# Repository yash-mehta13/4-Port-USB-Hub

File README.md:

# 4-Port USB Hub (USB Hub Port Extender)

A KiCad 8 design for a self-powered 4-port USB hub board. The schematic names a Genesys Logic **GL850G** hub controller (`IC1`, value `GL850G-HH`), one upstream USB-A connector (`J5`), four downstream USB-A connectors (`J1`–`J4`), a DC barrel-jack power input (`CN1`), per-port polyfuses, ferrite beads and bulk capacitors, SRV05-4 ESD arrays, a 12 MHz crystal, and a gang-mode LED.

> **Status: design in progress — not ready for fabrication.**
> A source-level audit (see [docs/validation-report.md](docs/validation-report.md)) found several connectivity defects in the schematic and PCB, including a **net that ties USB port 2's D− line to the 5 V rail**, **swapped D+/D− on port 1**, an **unconnected reset input**, and a **hub-controller symbol that is actually a Microchip MCP23017 I/O-expander symbol**. No board has been fabricated or tested, no KiCad ERC/DRC has been run (KiCad was not available in the audit environment), and no USB compliance claim is made. Details in [Known issues](#known-issues).

## Contents
[Purpose](#purpose) · [Images](#project-images) · [Design summary](#design-summary) · [Specifications](#specifications) · [Opening the project](#opening-the-project) · [Libraries and models](#custom-libraries-and-3d-models) · [Validation status](#validation-status) · [Known issues](#known-issues) · [BOM](#bill-of-materials) · [Fabrication](#fabrication-workflow) · [Safety](#safety-and-limitations) · [Docs](#documentation) · [License](#license-and-attribution) · [Roadmap](#future-improvements) · [Contributing](#contributing)

## Purpose
A USB hub turns one host USB port into several. This project is a learning/portfolio hardware design that implements a hub on a custom 4-layer board using a single-chip hub controller, with an external 5 V barrel-jack supply so downstream ports are not powered solely from the host. See [docs/project-overview.md](docs/project-overview.md).

## Project images
All images are real KiCad screenshots of this design (taken 2026-01-22/23, i.e. intermediate states of the design, not a verified final revision). **There is no photograph of a fabricated or assembled board in this repository.**

| | |
|---|---|
|  |  |
| 3D viewer, top view: five USB-A connectors, DC jack, HC-49 crystal, SSOP-28 hub IC. | 3D viewer, perspective: through-hole radial bulk capacitors, mixed horizontal connector styles. |

*Single-sheet schematic (A4, dated 2026-01-12): downstream ports, hub controller, reset, gang indicator, crystal, upstream, overcurrent network and external power.*

### Gallery
| Image | Content |
|---|---|
| [pcb-layout-all-layers.png](docs/images/pcb-layout-all-layers.png) | PCB editor, all layers visible, board with zone fills |
| [pcb-layout-bottom-active.png](docs/images/pcb-layout-bottom-active.png) | PCB editor, back copper highlighted (large "KiCad" logo text is on `B.Cu`) |
| [schematic-downstream-and-controller.png](docs/images/schematic-downstream-and-controller.png) | Downstream ports J1–J4 with IC2/IC3 and hub controller IC1 |
| [schematic-upstream-and-overcurrent.png](docs/images/schematic-upstream-and-overcurrent.png) | Upstream J5/IC4 and the overcurrent divider (R6/R7) |
| [schematic-reset-gang-crystal-power.png](docs/images/schematic-reset-gang-crystal-power.png) | Reset network, gang LED, crystal, external power and Q1 |

## Design summary
* **Controller:** `IC1`, value `GL850G-HH`, 28-pin SSOP footprint. Genesys Logic is the manufacturer *implied by the value*; the official datasheet could not be retrieved during the audit, so the pin map is **not verified** (see D1 in [circuit-design](docs/circuit-design.md)).
* **Upstream:** `J5` (Type-A) → `IC4` SRV05-4 → hub pins 25/26 (`USB0_N`/`USB0_P`). Upstream VBUS passes through ferrite `L1` to net `+5V`.
* **Downstream:** `J1`–`J4` ↔ `USB1`–`USB4` pairs on hub pins 27/28, 2/3, 8/9, 11/12; ESD arrays `IC2` (ports 1–2) and `IC3` (ports 3–4). Each port has a 500 mA-labelled polyfuse (`R1`–`R4`), ferrite bead (`L2`–`L5`), 100 µF + 0.1 µF.
* **Power:** barrel jack `CN1` → rail `VCC`; `Q1` (P-MOSFET) links `+5V` (host VBUS) and `VCC`. Hub analog rail `AVDD` is `DVDD` through ferrite `L6`.
* **Clock:** `Y1` 12 MHz, 2×33 pF.
* **Board:** 55 mm × 65 mm, 4 copper layers (`F.Cu`, `In1.Cu`=GND zone, `In2.Cu`=`+5V` zone, `B.Cu`), 1.6 mm. 45 vias (0.6/0.3 mm), all tracks 0.2 mm.

## Specifications
Only values read from the design files are listed.

| Item | Value | Source |
|---|---|---|
| Hub controller (per value field) | GL850G-HH, SSOP-28 footprint | schematic/PCB |
| Downstream / upstream connectors | 4 / 1 USB Type-A | schematic |
| Crystal | 12 MHz, 18 pF load (library description), 2×33 pF | schematic + library |
| Port polyfuses | value labelled 500 mA (part unspecified) | schematic |
| ESD arrays | 3× SRV05-4 | schematic |
| Board size | 55 × 65 mm | PCB Edge.Cuts |
| Layers / thickness | 4 / 1.6 mm (stackup in file; see caveats) | PCB |
| Net class | `USD_diff`: 0.2 mm width, 0.15 mm gap (applies to `USB*`) | project settings |
| Supply voltage, current budget, USB speed | **not specified in the design** | — |

USB speed is not asserted here: the supported speeds must be taken from the controller datasheet once the part is confirmed, and compliance has not been tested.

## Opening the project
1. Install KiCad 8.x (project files were saved by KiCad 8.0: schematic format `20231120`, PCB format `20240108`). KiCad 7 cannot open them.
2. Open `USB Hub Port Extender.kicad_pro`.
3. Standard KiCad libraries (symbols, footprints, `${KICAD8_3DMODEL_DIR}` 3D models) must be installed. The schematic embeds its symbols; footprints are resolved from KiCad's stock libraries.
4. Full steps: [docs/fabrication-guide.md](docs/fabrication-guide.md#reproducing-the-review).

## Custom libraries and 3D models
The root holds SnapEDA-style library downloads: `ECS-120-18-4X-CKM`, `MCP23017-E_SS`, `PMV20EN` (`.kicad_sym`, footprints, `.step`, `.zip`). **The current design instantiates none of their footprints**, and the repo has no `sym-lib-table`/`fp-lib-table`. Only the `ECS-120-18-4X-CKM` and `MCP23017-E_SS` *symbols* are embedded in the schematic (the latter wrongly, as `IC1`). See [docs/licensing-and-attribution.md](docs/licensing-and-attribution.md) and [circuit-design](docs/circuit-design.md#library-usage).

## Validation status
| Check | Status |
|---|---|
| KiCad ERC | **Not run** (KiCad 8 / `kicad-cli` unavailable) |
| KiCad DRC | **Not run** |
| Schematic ↔ PCB net comparison | Run with `tools/audit_netlist.py` (independent script): one difference (`J1` pin 5) |
| Gerber / drill / BOM / STEP export | **Not run** |
| Physical build, enumeration, USB compliance, ESD, thermal | **Not done** |

## Known issues
Full list with evidence: [docs/validation-report.md](docs/validation-report.md) and [docs/circuit-design.md](docs/circuit-design.md).

1. **D2 – VCC rail merged with `USB2_N`:** global label `USB2_N` sits on the VCC distribution wire; the PCB carries the same merged net. `J2` pin 2 (D−), `IC1` pins 2 and 23, SRV05-4 pins, `Q1`, `CN1` pin 1 and all four polyfuse inputs share one net.
2. **D3 – port 1 D+/D− swapped:** `J1` pin 2 (D−) is on `USB1_P`, pin 3 (D+) on `USB1_N`; `J2`–`J5` are wired D−→`_N`.
3. **D1 – `IC1` symbol is an MCP23017:** pin names (`GPA*`, `SCL`, `SDA`…) and SnapEDA properties belong to an I²C I/O expander.
4. **D4 – `RESET#` not connected to the reset RC network** (`R8`/`R9`/`C15`).
5. **D5 – overcurrent label typo:** `OVCURR1#` (R6/R7) vs `OVCURR#1` (IC1 pin 21).
6. **D6 – `J1` pin 5:** unconnected in schematic, `GND` in PCB.
7. Layout risks: 0.2 mm tracks carry VBUS/VCC; USB pair length mismatch (e.g. `USB4`); impedance unverified.

## Bill of materials
[docs/bill-of-materials.csv](docs/bill-of-materials.csv) – 54 parts grouped by value, matching all 54 PCB footprints. Most manufacturer part numbers are **unresolved** (the design stores generic values only); no sourcing links or prices are invented.

## Fabrication workflow
Summarised in [docs/fabrication-guide.md](docs/fabrication-guide.md). Do not order boards until the defects above are fixed, ERC/DRC are clean or justified, the fabricator's capabilities and stackup are agreed, and the impedance question is resolved.

## Safety and limitations
Unprotected tests of an unvalidated design can short VBUS to data lines or back-feed a host. Read [docs/safety-and-limitations.md](docs/safety-and-limitations.md) and [docs/hardware-validation.md](docs/hardware-validation.md) before powering any assembled board.

## Documentation
| Document | Purpose |
|---|---|
| [project-overview](docs/project-overview.md) | scope, artifacts, status |
| [circuit-design](docs/circuit-design.md) | schematic walkthrough and defects |
| [pcb-layout-review](docs/pcb-layout-review.md) | layers, routing, USB/power concerns |
| [bill-of-materials.csv](docs/bill-of-materials.csv) | components |
| [fabrication-guide](docs/fabrication-guide.md) | outputs and reproduction steps |
| [validation-report](docs/validation-report.md) | what was and wasn't run |
| [hardware-validation](docs/hardware-validation.md) | bench checklist (all unchecked) |
| [safety-and-limitations](docs/safety-and-limitations.md) | risks |
| [troubleshooting](docs/troubleshooting.md) | symptoms → causes |
| [decisions-and-roadmap](docs/decisions-and-roadmap.md) | design decisions and ideas |
| [licensing-and-attribution](docs/licensing-and-attribution.md) | license state |
| [docs/reports/](docs/reports/) | script-generated netlists/statistics |

## License and attribution
**No LICENSE file exists**, so no open-source permissions are granted by default; the owner must choose a license. Third-party library content (SnapEDA downloads, KiCad stock libraries) is covered in [docs/licensing-and-attribution.md](docs/licensing-and-attribution.md). Author: [yash-mehta13](https://github.com/yash-mehta13).

## Future improvements
See [docs/decisions-and-roadmap.md](docs/decisions-and-roadmap.md). Add a real board photograph and bench-test report once hardware exists.

## Contributing
See [CONTRIBUTING.md](CONTRIBUTING.md).

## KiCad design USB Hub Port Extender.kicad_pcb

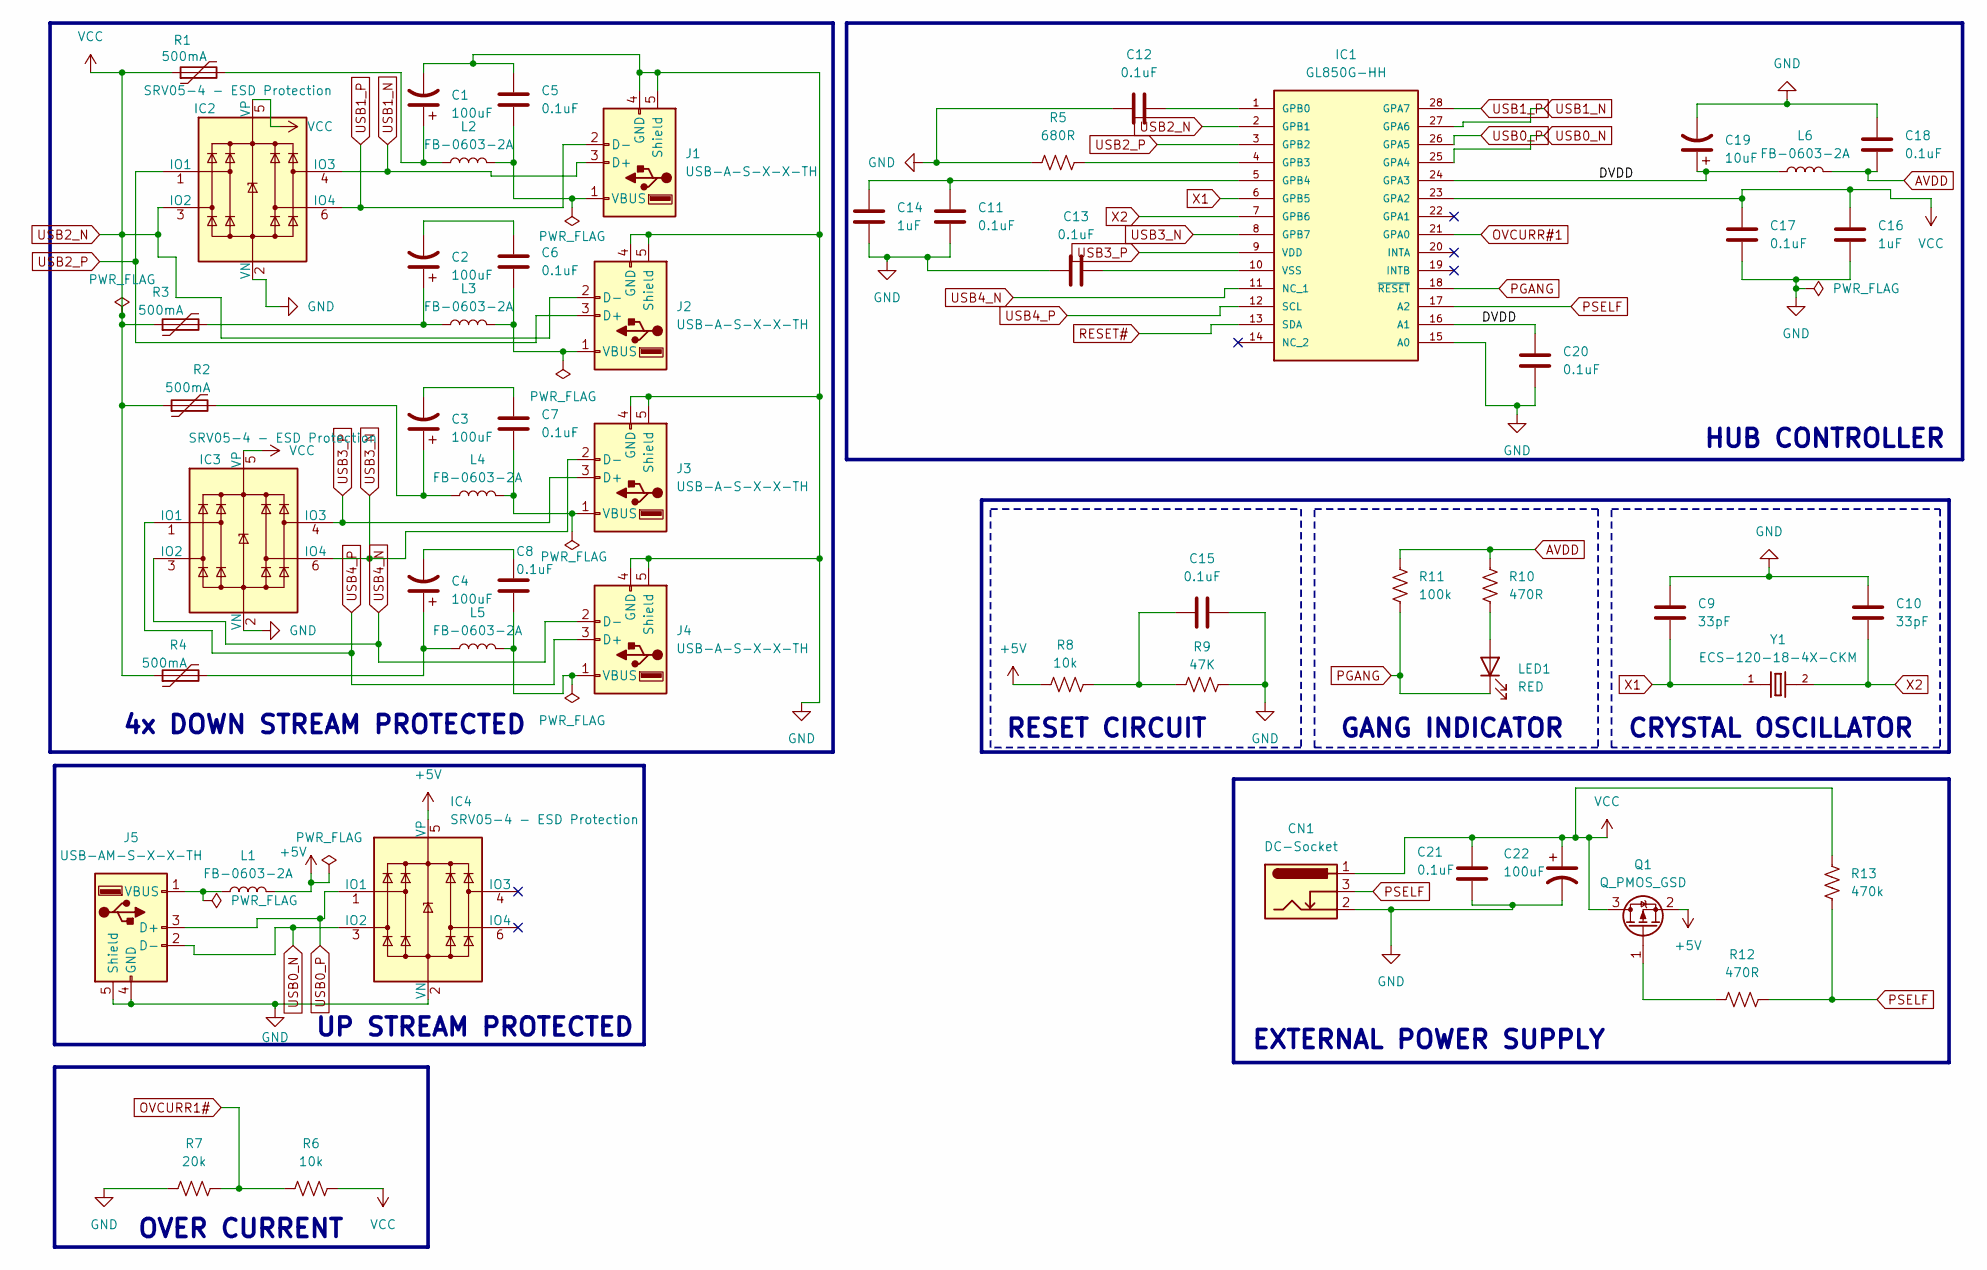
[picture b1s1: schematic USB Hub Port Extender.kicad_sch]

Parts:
C1, C2, C3, C4, C22: 100uF; CP_Radial_D5.0mm_P2.00mm
C5, C6, C7, C8, C11, C12, C13, C15, C17, C18, C20, C21: 0.1uF; C_0603_1608Metric
C9, C10: 33pF; C_0603_1608Metric
C14, C16: 1uF; C_0603_1608Metric
C19: 10uF; CP_Radial_D5.0mm_P2.00mm
CN1: DC-Socket; BarrelJack_Horizontal
IC1: GL850G-HH; SSOP-28_5.3x10.2mm_P0.65mm; Mouser_Part_Number 579-MCP23017-E/SS; DigiKey_Part_Number MCP23017-E/SS-ND
IC2, IC3, IC4: SRV05-4 - ESD Protection; SOT-23-6
J1, J2, J3: USB-A-S-X-X-TH; USB_A_Molex_67643_Horizontal
J4: USB-A-S-X-X-TH; USB_A_CNCTech_1001-011-01101_Horizontal
J5: USB-AM-S-X-X-TH; USB_A_Molex_48037-2200_Horizontal
L1, L2, L3, L4, L5, L6: FB-0603-2A; L_0603_1608Metric
LED1: RED; LED_0805_2012Metric
Q1: Q_PMOS_GSD; SOT-23
R1, R2, R3, R4: 500mA; R_0805_2012Metric
R5: 680R; R_0603_1608Metric
R6: 10k; R_0805_2012Metric
R7: 20k; R_0805_2012Metric
R8: 10k; R_0603_1608Metric
R9: 47K; R_0603_1608Metric
R10, R12: 470R; R_0805_2012Metric
R11: 100k; R_0805_2012Metric
R13: 470k; R_0805_2012Metric
Y1: ECS-120-18-4X-CKM; Crystal_SMD_HC49-SD; DigiKey_Part_Number 50-ECS-120-18-4X-CKM-ND

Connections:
+5V: IC4.5 (VP), L1.2, Q1.2 (S), R8.1
/DVDD: C19.1, C20.1, IC1.16 (A1), IC1.24 (GPA3), L6.1
AVDD: C18.2, L6.2, R10.1, R11.2
GND: C1.2, C5.2, C9.1, C10.1, C11.1, C12.1, C13.1, C14.1, C15.2, C16.2, C17.2, C18.1, C19.2, C20.2, C21.2, C22.2, CN1.2, IC1.15 (A0), IC2.2 (VN), IC3.2 (VN), IC4.2 (VN), J1.4 (GND), J1.5 (Shield), J2.4 (GND), J2.5 (Shield), J3.4 (GND), J3.5 (Shield), J4.4 (GND), J4.5 (Shield), J5.4 (GND), J5.5 (Shield), R5.1, R7.1, R9.2
unnamed: C1.1, L2.1, R1.2
unnamed: C2.1, L3.1, R3.2
unnamed: C2.2, C6.2
unnamed: C3.1, L4.1, R2.2
unnamed: C3.2, C7.2
unnamed: C4.1, L5.1, R4.2
unnamed: C4.2, C8.1
unnamed: C15.1, R8.2, R9.1
unnamed: C12.2, IC1.1 (GPB0)
unnamed: IC1.4 (GPB3), R5.2
unnamed: C11.2, C14.2, IC1.5 (GPB4)
unnamed: C13.2, IC1.10 (VSS)
unnamed: C5.1, J1.1 (VBUS), L2.2
unnamed: C6.1, J2.1 (VBUS), L3.2
unnamed: C7.1, J3.1 (VBUS), L4.2
unnamed: C8.2, J4.1 (VBUS), L5.2
unnamed: J5.1 (VBUS), L1.1
unnamed: LED1.2 (A), R10.2
unnamed: Q1.1 (G), R12.1
OVCURR1#: R6.1, R7.2
OVCURR#1: IC1.21 (GPA0)
PGANG: IC1.18 (~RESET), LED1.1 (K), R11.1
PSELF: CN1.3, IC1.17 (A2), R12.2, R13.2
RESET#: IC1.13 (SDA)
USB0_N: IC1.25 (GPA4), IC4.3 (IO2), J5.2 (D-)
USB0_P: IC1.26 (GPA5), IC4.1 (IO1), J5.3 (D+)
USB1_N: IC1.27 (GPA6), IC2.4 (IO3), J1.3 (D+)
USB1_P: IC1.28 (GPA7), IC2.6 (IO4), J1.2 (D-)
USB2_N: C16.1, C17.1, C21.1, C22.1, CN1.1, IC1.2 (GPB1), IC1.23 (GPA2), IC2.3 (IO2), IC2.5 (VP), IC3.5 (VP), J2.2 (D-), Q1.3 (D), R1.1, R2.1, R3.1, R4.1, R6.2, R13.1
USB2_P: IC1.3 (GPB2), IC2.1 (IO1), J2.3 (D+)
USB3_N: IC1.8 (GPB7), IC3.6 (IO4), J3.2 (D-)
USB3_P: IC1.9 (VDD), IC3.4 (IO3), J3.3 (D+)
USB4_N: IC1.11 (NC_1), IC3.3 (IO2), J4.2 (D-)
USB4_P: IC1.12 (SCL), IC3.1 (IO1), J4.3 (D+)
X1: C9.2, IC1.6 (GPB5), Y1.1
X2: C10.2, IC1.7 (GPB6), Y1.2

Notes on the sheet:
CRYSTAL OSCILLATOR
UP STREAM PROTECTED
HUB CONTROLLER
EXTERNAL POWER SUPPLY
4x DOWN STREAM PROTECTED
OVER CURRENT
GANG INDICATOR
RESET CIRCUIT

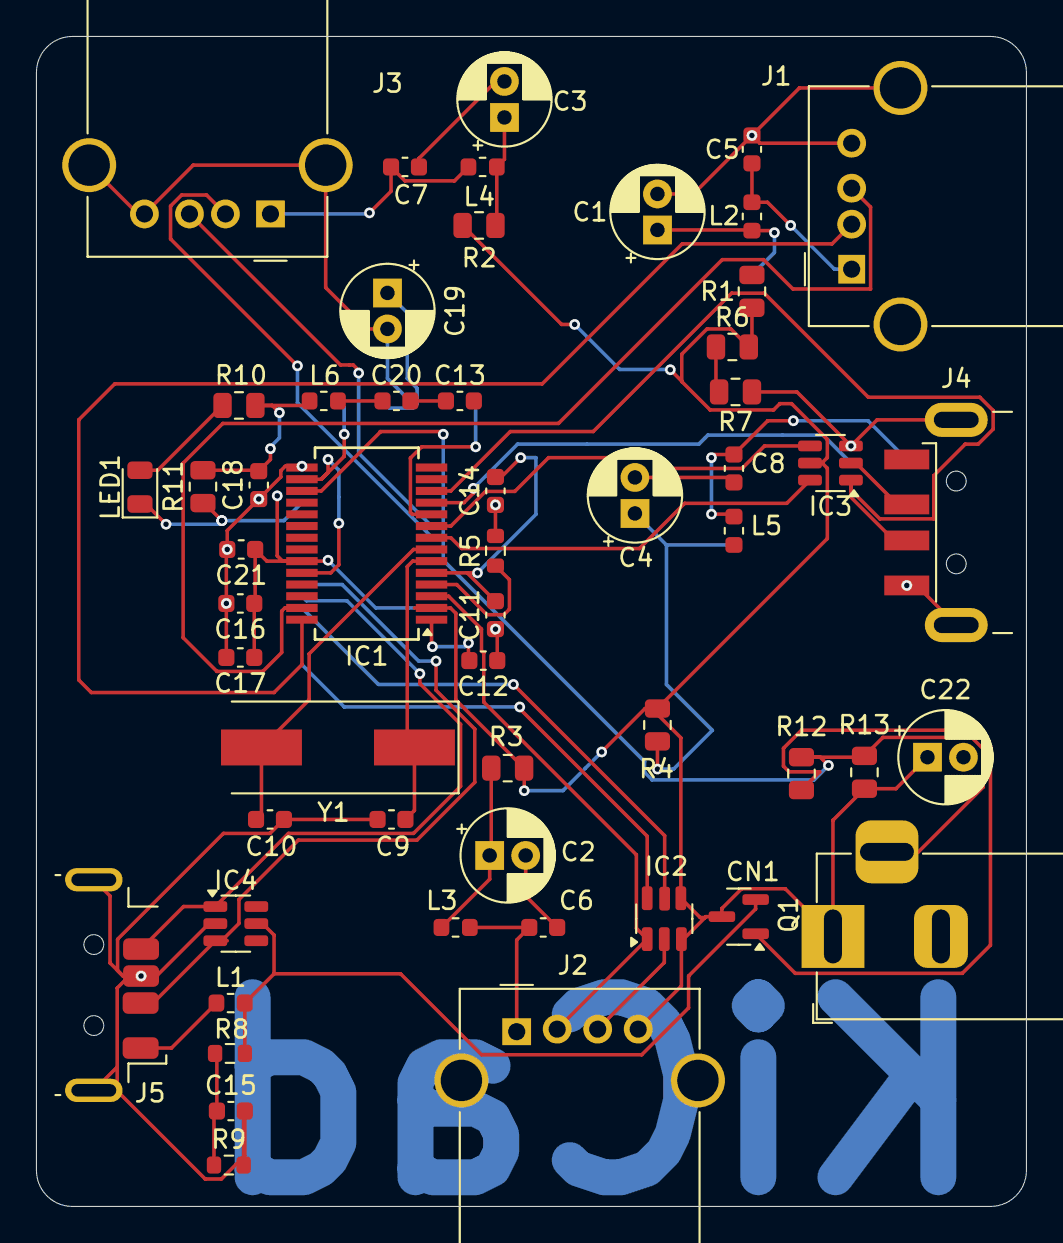
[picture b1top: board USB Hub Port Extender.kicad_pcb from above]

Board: 4 copper layers, 55.0 x 65.0 mm, 54 parts (0 on the bottom side), 38 nets.

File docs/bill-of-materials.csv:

References,Qty,Value (schematic),Description,Manufacturer,Manufacturer part number,Footprint,Datasheet,Sourcing link,Notes,Population status
"J1, J2, J3",3,USB-A-S-X-X-TH,"USB Type-A receptacle, downstream (J1 port 1, J2 port 2, J3 port 3)",unresolved,unresolved,Connector_USB:USB_A_Molex_67643_Horizontal,,,"Through-hole; schematic value is a generic string, not an MPN. Footprint name suggests Molex 67643 series - confirm part vs footprint before ordering.",Populate
J4,1,USB-A-S-X-X-TH,"USB Type-A plug/receptacle, downstream port 4",unresolved,unresolved,Connector_USB:USB_A_CNCTech_1001-011-01101_Horizontal,,,"Different footprint family from J1-J3 (CNC Tech 1001-011-01101 footprint, SMD + TH shield). Confirm actual part; 3D view shows a plug-style body.",Populate
J5,1,USB-AM-S-X-X-TH,"USB Type-A connector, upstream port to host",unresolved,unresolved,Connector_USB:USB_A_Molex_48037-2200_Horizontal,,,Edge-mounted footprint. Footprint name suggests Molex 48037-2200 - confirm.,Populate
CN1,1,DC-Socket,DC barrel jack with switch (external power input),unresolved,unresolved,Connector_BarrelJack:BarrelJack_Horizontal,,,"Barrel dimensions, voltage and current rating are not stated in the design. Input voltage must be 5 V-class per the VCC rail and USB loads; not specified in files.",Populate
IC1,1,GL850G-HH,USB 2.0 hub controller (per schematic value),Genesys Logic (per value; not verified in files),unresolved (value GL850G-HH),Package_SO:SSOP-28_5.3x10.2mm_P0.65mm,,,DEFECT: symbol/properties are for Microchip MCP23017-E/SS (I2C IO expander). Do NOT order MCP23017. Replace symbol with a verified GL850G symbol and verify package against the datasheet.,Populate after symbol fix
"IC2, IC3, IC4",3,SRV05-4,"4-channel TVS/ESD array, SOT-23-6",onsemi (per symbol datasheet link),SRV05-4 (per symbol value; exact ordering code unresolved),Package_TO_SOT_SMD:SOT-23-6,http://www.onsemi.com/pub/Collateral/SRV05-4-D.PDF,,IC2: ports J1/J2 D+/D-; IC3: ports J3/J4; IC4: upstream J5. Connectivity defects documented in docs/circuit-design.md.,Populate
Q1,1,Q_PMOS_GSD,"P-channel MOSFET, SOT-23, upstream/external power switchover",unresolved,unresolved,Package_TO_SOT_SMD:SOT-23,,,Generic KiCad symbol. Part not selected; Vgs/Rds(on)/body-diode behaviour must be chosen and analysed. The custom PMV20EN files in the repo are N-channel and are NOT used.,Populate once part selected
Y1,1,ECS-120-18-4X-CKM,"12 MHz crystal, 18 pF load, HC-49/US (per library description)",ECS Inc. (per library property),ECS-120-18-4X-CKM,Crystal:Crystal_SMD_HC49-SD,,,"Placed footprint is the KiCad stock SMD HC49-SD, not the custom through-hole XTAL_ECS-120-18-4X-CKM footprint. Confirm the real part's land pattern fits.",Populate
"R1, R2, R3, R4",4,500mA,Resettable PTC fuse (symbol Device:Polyfuse); one per downstream port VBUS,unresolved,unresolved,Resistor_SMD:R_0805_2012Metric,,,"Value field is a current label only; hold/trip current, voltage and part are unspecified. The 0805 resistor footprint must match the chosen PPTC.",Populate once part selected
"L1, L2, L3, L4, L5, L6",6,FB-0603-2A,"Ferrite bead, 0603, 2 A (per value)",unresolved,unresolved,Inductor_SMD:L_0603_1608Metric,,,L1: upstream VBUS; L2-L5: downstream VBUS; L6: AVDD from DVDD. Impedance and DC resistance unspecified.,Populate
"C1, C2, C3, C4, C22",5,100uF,"Polarized capacitor, radial D5.0 mm, 2.0 mm pitch",unresolved,unresolved,Capacitor_THT:CP_Radial_D5.0mm_P2.00mm,,,C1-C4: per-port VBUS bulk; C22: VCC bulk. Voltage rating not specified.,Populate
C19,1,10uF,"Polarized capacitor, radial D5.0 mm, 2.0 mm pitch",unresolved,unresolved,Capacitor_THT:CP_Radial_D5.0mm_P2.00mm,,,DVDD/AVDD area bulk. Voltage rating not specified.,Populate
"C5, C6, C7, C8, C11, C12, C13, C15, C17, C18, C20, C21",12,0.1uF,Ceramic capacitor 0603,unresolved,unresolved,Capacitor_SMD:C_0603_1608Metric,,,Dielectric and voltage not specified.,Populate
"C14, C16",2,1uF,Ceramic capacitor 0603,unresolved,unresolved,Capacitor_SMD:C_0603_1608Metric,,,Dielectric and voltage not specified.,Populate
"C9, C10",2,33pF,Ceramic capacitor 0603 (crystal load),unresolved,unresolved,Capacitor_SMD:C_0603_1608Metric,,,Dielectric (C0G/NP0 typical) not specified.,Populate
R5,1,680R,Resistor 0603,unresolved,unresolved,Resistor_SMD:R_0603_1608Metric,,,Between IC1 pin 4 and GND.,Populate
R8,1,10k,"Resistor 0603 (reset divider, to +5V)",unresolved,unresolved,Resistor_SMD:R_0603_1608Metric,,,Reset network is not connected to IC1 RESET# - see defects.,Populate
R9,1,47K,"Resistor 0603 (reset divider, to GND)",unresolved,unresolved,Resistor_SMD:R_0603_1608Metric,,,,Populate
R6,1,10k,"Resistor 0805 (overcurrent bias, to VCC)",unresolved,unresolved,Resistor_SMD:R_0805_2012Metric,,,Net label mismatch OVCURR1# vs OVCURR#1 - see defects.,Populate
R7,1,20k,"Resistor 0805 (overcurrent bias, to GND)",unresolved,unresolved,Resistor_SMD:R_0805_2012Metric,,,,Populate
"R10, R12",2,470R,Resistor 0805,unresolved,unresolved,Resistor_SMD:R_0805_2012Metric,,,R10: gang-indicator LED series; R12: Q1 gate network.,Populate
R11,1,100k,Resistor 0805,unresolved,unresolved,Resistor_SMD:R_0805_2012Metric,,,PGANG pull-up to AVDD.,Populate
R13,1,470k,Resistor 0805,unresolved,unresolved,Resistor_SMD:R_0805_2012Metric,,,VCC to PSELF.,Populate
LED1,1,RED,Red LED 0805,unresolved,unresolved,LED_SMD:LED_0805_2012Metric,,,Gang-mode indicator per schematic text. Forward voltage/current not specified.,Populate

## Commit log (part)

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2026-01-22 Initial commit of USB Hub
2026-01-22 Initial USB Hub design
